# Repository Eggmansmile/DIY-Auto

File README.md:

# DIY Auto — V1

RC car: ESP32 + TB6612FNG motor driver, two rear DC motors, servo steering, 2S Li-ion battery.
Everything is generated from code. Edit the script, not the output.

Assembly video: [Video/DIYAuto_assembly_v1.mp4](Video/DIYAuto_assembly_v1.mp4)

## PCB (rev 9)

| Top | Bottom |
|---|---|
|  |  |

The TB6612 module plugs into J8/J9, the ESP32 DevKit into J2/J3. The LM2596 buck module sits on J6/J7 on a printed spacer: set it to 5.0 V before you connect J7.
Order `KiCad/DIY-Auto_rev9_gerbers_PCBWay.zip`.

Schematic: [docs/schematic.svg](docs/schematic.svg) (PDF: [KiCad/DIY-Auto_schema.pdf](KiCad/DIY-Auto_schema.pdf))

## Files

| Folder | What |
|---|---|
| `Scripts/cad/` | SolidCraft CAD (`CAD/DIY-Auto.sc`). Dimensions in `params.py`, `export_sc.py` writes STEP/STL to `CAD/parts/`, `check_all.py` checks collisions, `plates.py` makes print plates. |
| `CAD/` | Generated STEP/STL per subassembly (`print/` = print orientation), print plates (`.3mf`), SolidCraft master `DIY-Auto.sc`, `BOM.md`. |
| `Scripts/` | `gen_schematic.py` → `gen_pcb.py` → `route_pcb.py` → `silk_pcb.py` (KiCad), `gen_fritzing.py` (breadboard). |
| `KiCad/` | Schematic, PCB, gerbers. |
| `Fritzing/` | Breadboard layout for testing before the PCB arrives. |
| `Firmware/` | Arduino test sketches (`test_drive`, `test_tb6612`, `pintest`, `debug_hold`). |
| `Video/` | Assembly animation: Blender script (`assembly_anim.py`, steps in `steps.json`) + Remotion title cards. |
| `*.md` | Build notes (Dutch, Obsidian): electronics, mechanics, BOM, assembly, firmware. |

Not included: the SpringRC SM-S2309S servo model (Thingiverse 2835648) and the LM2596 module model used in the renders ([KiCad-Chinese_Modules](https://github.com/yet-another-average-joe/KiCad-Chinese_Modules)), because neither comes with a licence that allows redistribution. Without the LM2596 model, the video script uses the plain box from the CAD.

## Licence

- Code (`Scripts/`, `Firmware/`, `Video/` scripts): [MIT](LICENSE)
- Hardware design (`CAD/`, `KiCad/`, `Fritzing/`, `Drawings/`) and notes: [CERN-OHL-P-2.0](LICENSE-HARDWARE)

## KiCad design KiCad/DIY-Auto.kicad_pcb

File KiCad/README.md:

# DIY-Auto — KiCad

Schema van de RC-auto: accu, ESP32 DevKit-headers en twee H-bruggen met losse MOSFETs.
Volledige uitleg staat in de note `../DIY Auto.md`.

## Breadboard openen (dit vergeet je telkens)

Het breadboard zit **niet** in de projectlijst van KiCad, want die toont `.kicad_bbrd` niet.

1. `DIY-Auto.kicad_pro` openen → **PCB Editor**.
2. Breadboard-icoon in de rechtse werkbalk.
3. In **dat venster** (onderdelenlade links, "Binding posts" rechts): **File → Load session… (Ctrl+L)**.
4. `DIY-Auto.kicad_bbrd` kiezen → **Validate**.

Controle: de statusbalk zegt `Session loaded from …`. Staat er `Loaded 40 component(s) from DIY-Auto.net`, dan heb je de netlist geladen in plaats van de sessie, en blijft het bord leeg.

Let op: het File-menu van de projectmanager heeft geen *Load session*. Dat menu-item bestaat alleen in het breadboard-venster.

## Legenda van de breadboardtekening

Twee beelden in `../../../Assets/`:

- `DIY-Auto_breadboard.png` — vier bouwstappen onder elkaar. Elke stap toont enkel wat er bijkomt; het vorige werk staat grijs weggevaagd.
- `DIY-Auto_breadboard-overzicht.png` — alles in één beeld.

Alles staat op ware grootte: 1 gat = 2,54 mm.

Bouwvolgorde: 1) voedingsrails en condensatoren, 2) hoge kant, 3) lage kant en motorgaten, 4) draden naar de ESP32 en de testlast. De accu sluit je als laatste aan.

### Draden

| Kleur | Betekenis |
|---|---|
| Rood | +11,1 V van de accu |
| Zwart | GND, de min van de accu |
| Blauw | signaal van de ESP32 naar een gate of basis |
| Grijs | verbinding tussen twee gaten op het bord |

### Onderdelen

| Vorm | Wat | Maat |
|---|---|---|
| Beige blokje | weerstand | 6,3 × 2,5 mm |
| Oranje schijfje | keramische condensator 100 nF | 5 mm |
| Blauwe cilinder met witte streep | elco 470 µF, streep = min | 10 mm |
| Grijs blok met lichte strip boven | TO-220 MOSFET, strip = metalen tab | 10 × 15 mm |
| Zwarte halve cilinder | TO-92 2N3904 | 5 mm |
| Rode of groene bol | led van de testlast | 5 mm |

De TO-220's zijn half doorzichtig getekend, anders zie je de gaten en draden eronder niet meer.

### Tekens

| Teken | Betekenis |
|---|---|
| Gekleurd bolletje met tekstlabel | gat waar een draad van de ESP32 in komt, met het GPIO-nummer erbij |
| Streepjescirkel met M+ of M− | hier komen de twee motordraden |
| Geel bolletje links | accudraad, via de zekering en de schakelaar |
| `G D S` onder een TO-220 | gate, drain, source, van links naar rechts |
| `C B E` onder een TO-92 | collector, basis, emitter, van links naar rechts |
| Schaalbalk onderaan | 10 gaten = 25,4 mm |

### Richting van de onderdelen

- **TO-220 (IRF9540N, IRLZ44N):** tekstkant naar jou, metalen tab naar rij a.
- **TO-92 (2N3904):** platte kant van je weg, naar rij a. Dan staan de pootjes C B E, net als op de tekening.
- **Elco:** de witte streep is de min en gaat naar GND.

### Verbindingen op het bord

- Rijen a–e en f–j: elke rij van 5 gaten is onderling verbonden. De gleuf in het midden scheidt boven en onder.
- De + en − rails zijn halverwege onderbroken. Leg daar een draadje over, anders staat de rechterhelft dood.

## Bestanden

| Bestand | Wat |
|---|---|
| `DIY-Auto.kicad_sch` | Schema. **Wordt overschreven door het script** |
| `DIY-Auto.net` | Netlist, invoer voor de breadboardtekening |
| `DIY-Auto.kicad_bbrd` | Breadboardsessie voor de plugin Breadboard Builder |
| `DIY-Auto_schema.pdf` | Export om af te drukken |
| `.history/` | Automatische back-ups van KiCad zelf |

## Opnieuw genereren

Alles gebeurt vanuit de projectmap één niveau hoger:

```
cd ~/Personal\ Projects/Second\ brain/Projects/DIY\ Auto\ Project
```

Schema:

```
KICAD_SYMBOL_DIR=/usr/share/kicad/symbols ~/Personal\ Projects/DIY-Auto/.venv/bin/python Scripts/gen_schematic.py
kicad-cli sch erc KiCad/DIY-Auto.kicad_sch
kicad-cli sch export netlist -o KiCad/DIY-Auto.net KiCad/DIY-Auto.kicad_sch
kicad-cli sch export pdf -o KiCad/DIY-Auto_schema.pdf KiCad/DIY-Auto.kicad_sch
```

Breadboardtekening en sessiebestand:

```
~/Personal\ Projects/DIY-Auto/.venv/bin/python Scripts/gen_breadboard.py KiCad/DIY-Auto.net ../../Assets/DIY-Auto_breadboard.png KiCad/DIY-Auto.kicad_bbrd
```

Dat script controleert zichzelf tegen de netlist en moet `OK: 14 netten identiek aan KiCad` printen.

**Sluit KiCad voor je het schema opnieuw genereert.** Het script overschrijft `DIY-Auto.kicad_sch`, dus wat je in KiCad zelf tekende, is dan weg.

## Bekende waarschuwingen

4× `lib_symbol_mismatch` bij de 2N3904. Die komen doordat het script afgeleide symbolen anders inbedt dan KiCad. Elektrisch verandert er niets. Opruimen kan met **Tools → Update Symbols from Library**, maar doe dat pas als je niets meer genereert.

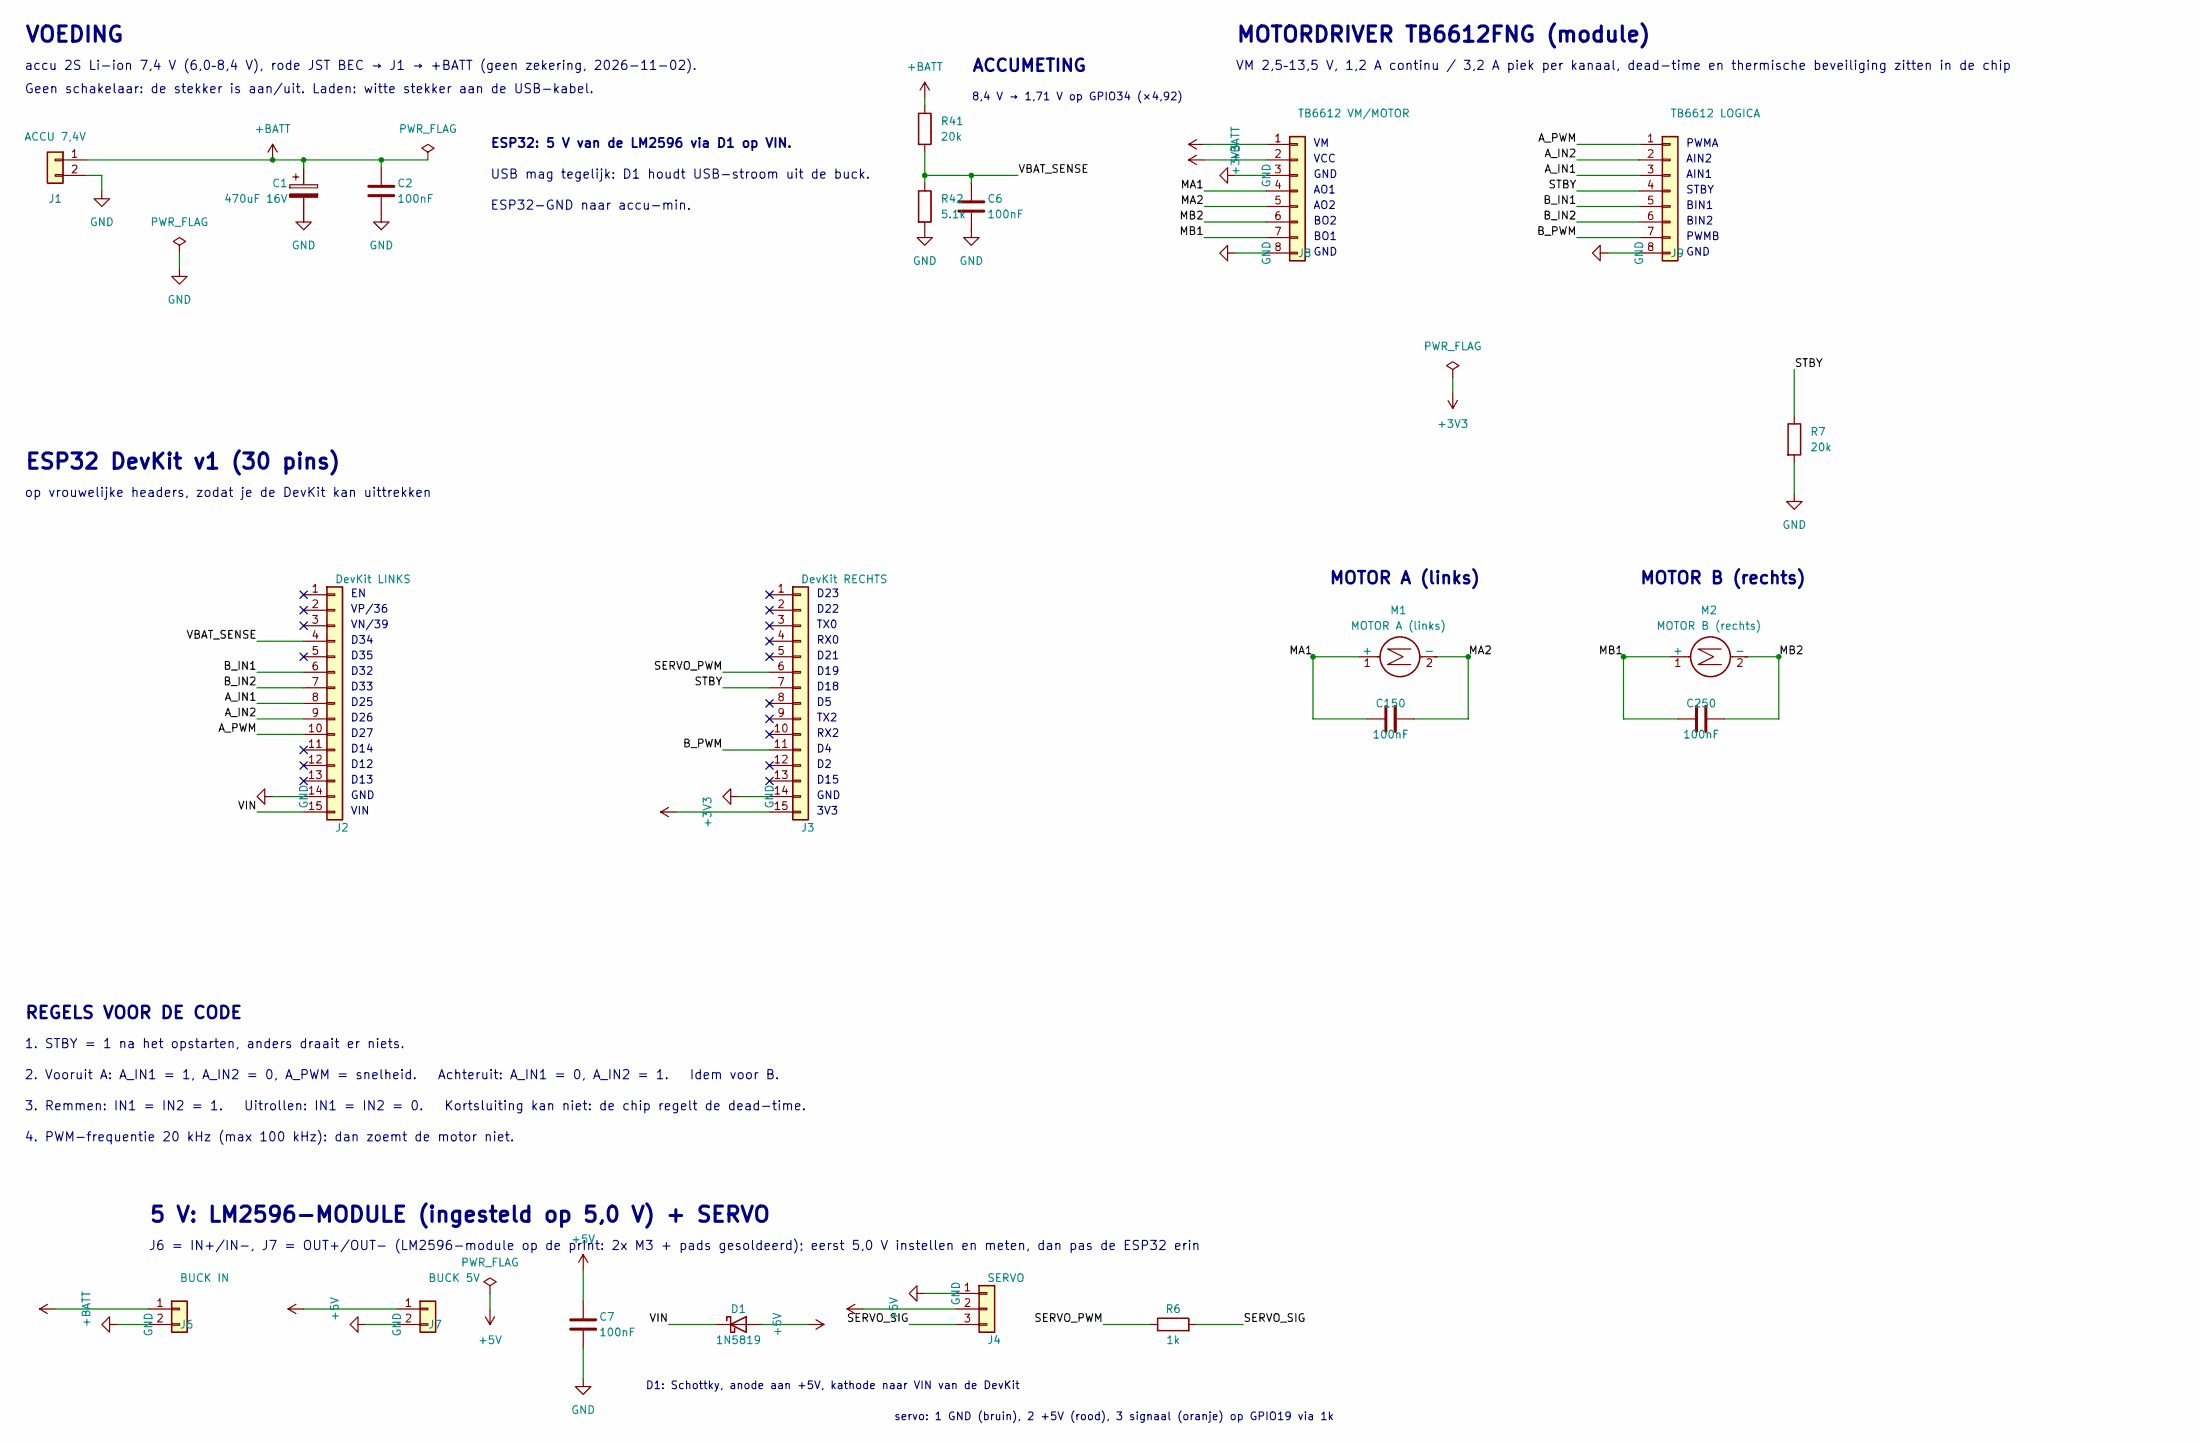
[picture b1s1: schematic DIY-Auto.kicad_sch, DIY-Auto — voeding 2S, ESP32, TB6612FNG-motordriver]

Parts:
C1: 470uF 16V; CP_Radial_D10.0mm_P5.00mm
C2, C6, C7, C150, C250: 100nF; C_Disc_D5.0mm_W2.5mm_P5.00mm
D1: 1N5819; D_DO-41_SOD81_P10.16mm_Horizontal
J1: ACCU 7,4V; TerminalBlock_Phoenix_MKDS-1,5-2_1x02_P5.00mm_Horizontal
J2: DevKit LINKS; PinSocket_1x15_P2.54mm_Vertical
J3: DevKit RECHTS; PinSocket_1x15_P2.54mm_Vertical
J4: SERVO; PinHeader_1x03_P2.54mm_Vertical
J6: BUCK IN; LM2596_IN
J7: BUCK 5V; LM2596_OUT
J8: TB6612 VM/MOTOR; PinSocket_1x08_P2.54mm_Vertical
J9: TB6612 LOGICA; PinSocket_1x08_P2.54mm_Vertical
M1: MOTOR A (links); TerminalBlock_Phoenix_MKDS-1,5-2_1x02_P5.00mm_Horizontal
M2: MOTOR B (rechts); TerminalBlock_Phoenix_MKDS-1,5-2_1x02_P5.00mm_Horizontal
R6: 1k; R_Axial_DIN0207_L6.3mm_D2.5mm_P10.16mm_Horizontal
R7, R41: 20k; R_Axial_DIN0207_L6.3mm_D2.5mm_P10.16mm_Horizontal
R42: 5.1k; R_Axial_DIN0207_L6.3mm_D2.5mm_P10.16mm_Horizontal

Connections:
+3V3: J3.15, J8.2
+5V: C7.1, D1.2 (A), J4.2, J7.1
+BATT: C1.1, C2.1, J1.1, J6.1, J8.1, R41.1
/A_IN1: J2.8, J9.3
/A_IN2: J2.9, J9.2
/A_PWM: J2.10, J9.1
/B_IN1: J2.6, J9.5
/B_IN2: J2.7, J9.6
/B_PWM: J3.11, J9.7
/MA1: C150.1, J8.4, M1.1 (+)
/MA2: C150.2, J8.5, M1.2 (-)
/MB1: C250.1, J8.7, M2.1 (+)
/MB2: C250.2, J8.6, M2.2 (-)
/SERVO_PWM: J3.6, R6.1
/SERVO_SIG: J4.3, R6.2
/STBY: J3.7, J9.4, R7.1
/VBAT_SENSE: C6.1, J2.4, R41.2, R42.1
/VIN: D1.1 (K), J2.15
GND: C1.2, C2.2, C6.2, C7.2, J1.2, J2.14, J3.14, J4.1, J6.2, J7.2, J8.3, J8.8, J9.8, R7.2, R42.2

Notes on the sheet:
VOEDING
accu 2S Li-ion 7,4 V (6,0–8,4 V), rode JST BEC → J1 → +BATT (geen zekering, 2026-11-02).
Geen schakelaar: de stekker is aan/uit. Laden: witte stekker aan de USB-kabel.
ESP32: 5 V van de LM2596 via D1 op VIN.
USB mag tegelijk: D1 houdt USB-stroom uit de buck.
ESP32-GND naar accu-min.
ACCUMETING
8,4 V → 1,71 V op GPIO34 (×4,92)
ESP32 DevKit v1 (30 pins)
op vrouwelijke headers, zodat je de DevKit kan uittrekken
VP/36
VN/39
D34
D35
D32
D33
D25
D26
D27
D14
D12
D13
GND
VIN
D23
D22
TX0
RX0
D21
D19
D18
TX2
RX2
D15
3V3
5 V: LM2596-MODULE (ingesteld op 5,0 V) + SERVO
J6 = IN+/IN-, J7 = OUT+/OUT- (LM2596-module op de print: 2x M3 + pads gesoldeerd); eerst 5,0 V instellen en meten, dan pas de ESP32 erin
D1: Schottky, anode aan +5V, kathode naar VIN van de DevKit
servo: 1 GND (bruin), 2 +5V (rood), 3 signaal (oranje) op GPIO19 via 1k
MOTORDRIVER TB6612FNG (module)

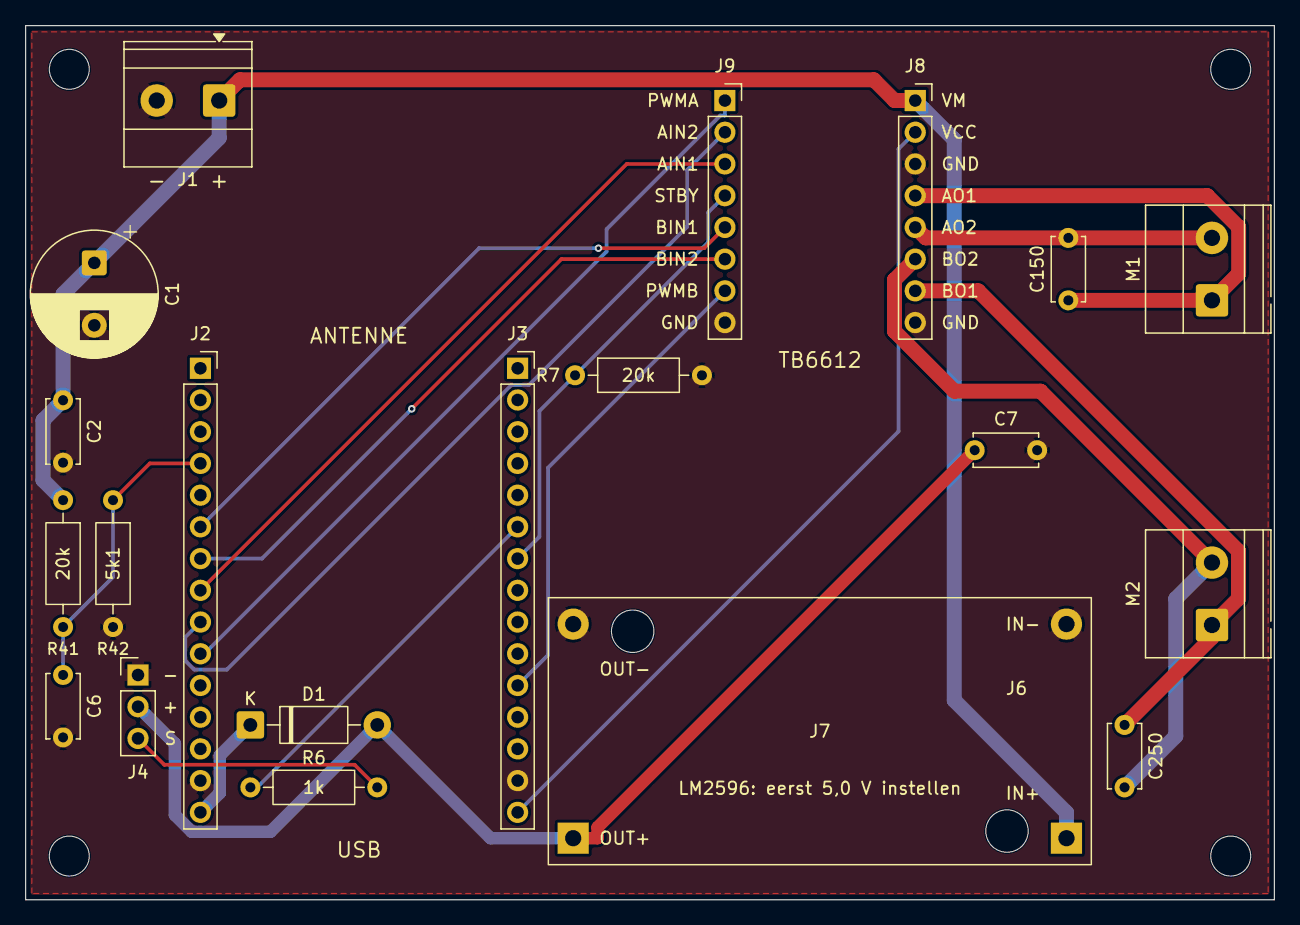
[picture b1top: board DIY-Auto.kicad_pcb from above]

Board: 2 copper layers, 100.0 x 70.0 mm, 25 parts (0 on the bottom side), 19 nets.

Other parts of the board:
H1, H2, H3, H4: MountingHole_3.2mm_M3
